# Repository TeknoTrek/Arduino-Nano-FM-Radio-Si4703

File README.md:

# FM Radio Project with Arduino Nano and Si4703

This project is an FM radio built using the Arduino Nano, Si4703 FM module, PAM8403 stereo amplifier module, rotary encoder, and a 16x02 LCD display. It is designed to tune FM frequencies and provide stereo audio output through speakers.

## Project Components

- **Arduino Nano**: Used as the microcontroller.
- **Si4703 FM Radio Module**: Receives FM radio signals.
- **PAM8403 Stereo Amplifier Module**: Amplifies the audio output.
- **Rotary Encoder**: Used for tuning the frequency and adjusting the volume.
- **16x02 LCD Display**: Displays the current FM frequency.

## Project Files

This repository includes the following files:

- **Schematic**: Circuit schematic created using KiCad.
- **PCB Design**: Printed Circuit Board (PCB) design made with KiCad.
- **3D Models**: 3D models of the components used in the project.
- **Code**: Arduino code to control the FM radio module and display frequencies on the LCD.

## Requirements

To run this project, you'll need:
- Arduino IDE (version 1.8.2 or newer)
- Si4703 Arduino library
- KiCad (for viewing the schematic and PCB design)

## Installation

1. **Install Arduino IDE** and add the Si4703 library.
2. Upload the `.ino` file from this repository to the Arduino Nano.
3. Connect the components as per the circuit schematic.
4. Power the device, and use the rotary encoder to tune the radio frequency.

## Watch the Build Process

You can watch the full build process of this FM Radio on my YouTube channel [**Teknotrek**](https://www.youtube.com/@TeknoTrek). Click the link below to see how the circuit is assembled, soldered, and tested:

[Watch on YouTube](https://www.youtube.com/watch?v=up5PCYIprFo)

## Project Images

- 3D models of the components and the assembled circuit.
- Front and back views of the PCB.
- Real images of the completed project.

## Circuit Schematic

## PCB Layout

## 3D Model

A 3D model of the assembled PCB is included to give you a better idea of how the final product will look.

## License

This project is licensed under the MIT License. See the LICENSE file for more details.

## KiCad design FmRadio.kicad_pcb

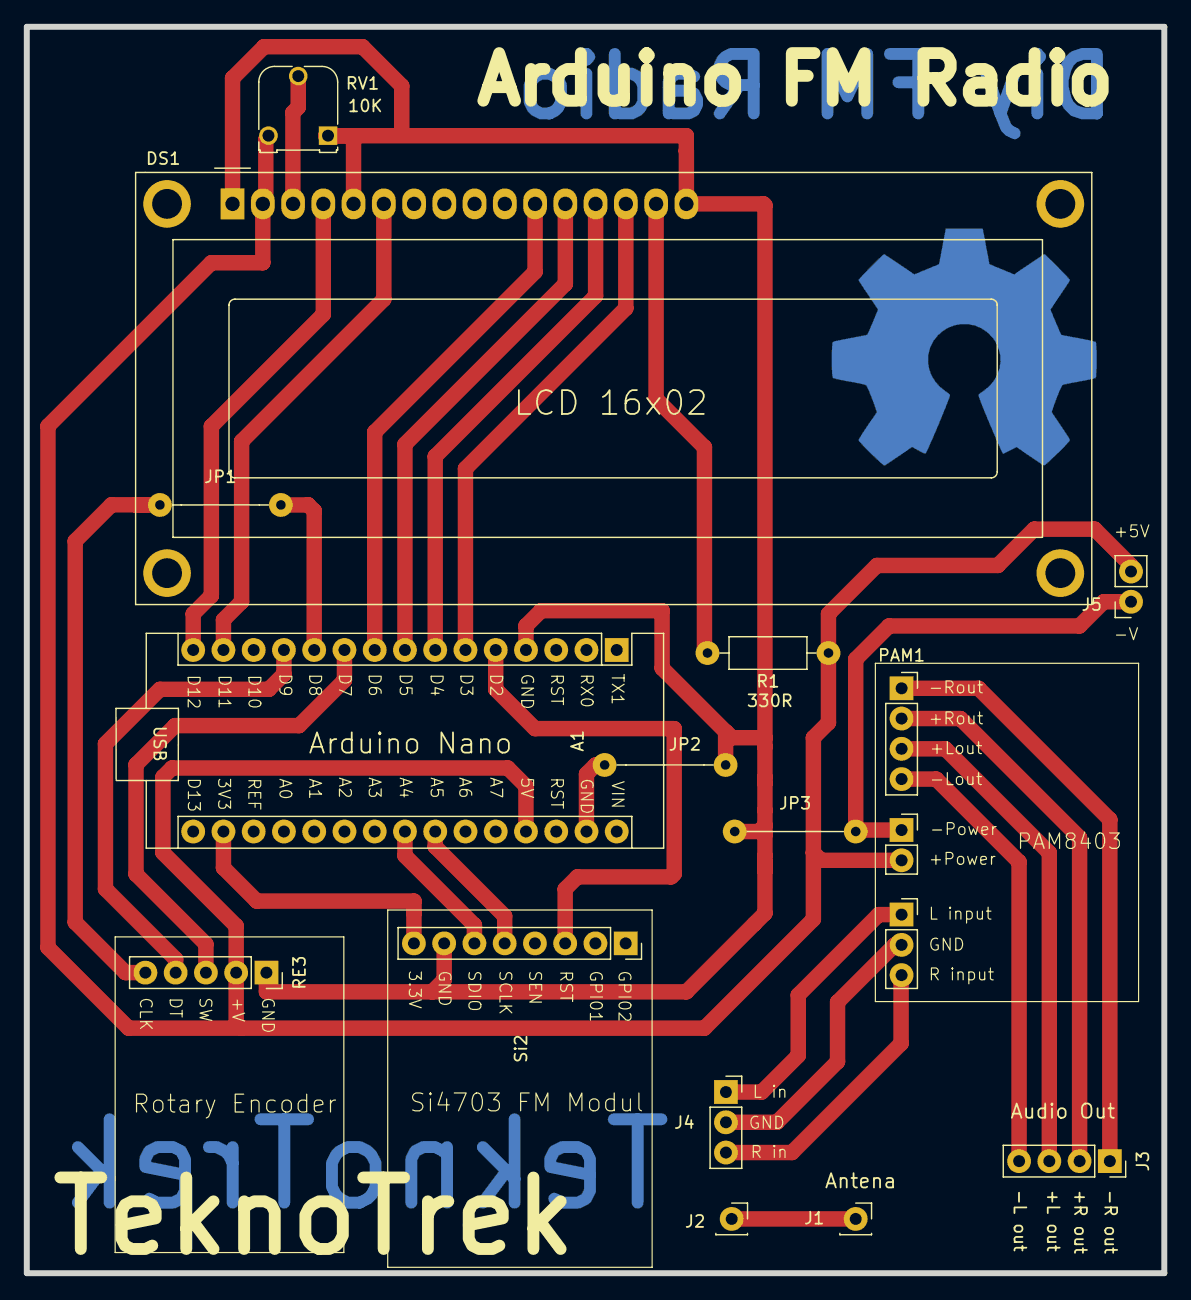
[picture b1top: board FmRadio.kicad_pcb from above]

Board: 2 copper layers, 95.5 x 104.6 mm, 15 parts (0 on the bottom side), 28 nets.

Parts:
A1: Arduino_Nano; Arduino_Nano_VER2
DS1: WC1602A
J1, J2: Conn_01x01_Pin; PinSocket_1x01_P2.54mm_Vertical
J3: Conn_01x04_Pin; PinSocket_1x04_P2.54mm_Vertical
J4: Conn_01x03_Pin; PinSocket_1x03_P2.54mm_Vertical
J5: Conn_01x02_Pin; PinSocket_1x02_P2.54mm_Vertical
JP1, JP2, JP3: Jumper_2_Bridged; Jumper_Atlama
PAM1: PAM8403; GF1002
R1: R; R_Axial_DIN0207_L6.3mm_D2.5mm_P10.16mm_Horizontal
RE3: R. Encoder Modul; Rotary_Encoder_Modul_Footer
RV1: R_Potentiometer; Potentiometer_Runtron_RM-065_Vertical
Si2: Si4703 FM Module; Si4703

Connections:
unnamed: A1.17 (3V3), Si2.8 (3.3V)
unnamed: A1.27 (+5V), DS1.2 (VDD), J5.2, PAM1.6 (+Power), R1.1, RE3.2 (+V), RV1.1
unnamed: A1.23 (A4), Si2.6 (SDIO)
unnamed: A1.24 (A5), Si2.5 (SCLK)
unnamed: A1.5 (D2), Si2.3 (RST)
unnamed: A1.6 (D3), DS1.14 (D7)
unnamed: A1.7 (D4), DS1.13 (D6)
unnamed: A1.8 (D5), DS1.12 (D5)
unnamed: A1.9 (D6), DS1.11 (D4)
unnamed: A1.10 (D7), RE3.3 (SW)
unnamed: A1.11 (D8), JP1.2 (B)
unnamed: A1.12 (D9), RE3.4 (DT)
unnamed: A1.14 (D11), DS1.6 (E)
unnamed: A1.15 (D12), DS1.4 (RS)
unnamed: DS1.15 (LED(+)), R1.2
unnamed: A1.4 (GND), DS1.1 (VSS), DS1.5 (R/W), DS1.16 (LED(-)), JP2.2 (B), JP3.1 (A), RE3.1 (GND), RV1.3, Si2.7 (GND)
unnamed: DS1.3 (VO), RV1.2
unnamed: J1.1, J2.1
unnamed: J3.1, PAM1.1 (-Rout)
unnamed: J3.2, PAM1.2 (+Rout)
unnamed: J3.3, PAM1.3 (+Lout)
unnamed: J3.4, PAM1.4 (-Lout)
unnamed: J4.1, PAM1.7 (L_input)
unnamed: J4.2, PAM1.8 (GND)
unnamed: J4.3, PAM1.9 (R_input)
unnamed: J5.1, JP3.2 (B), PAM1.5 (-Power)
unnamed: JP1.1 (A), RE3.5 (CLK)
unnamed: A1.29 (GND), JP2.1 (A)
